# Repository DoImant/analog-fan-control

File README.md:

# Description:

This fan control circuit was realized with an LM317 voltage regulator. The circuit is suitable for fans that cannot be regulated via PWM (2 or 3-pin).
The maximum operating voltage is 12V. An NTC 10K 3950 (1%) with JST XH cable connector is used for temperature measurement.
The circuit board is equipped with a four-pin fan connector. If a fan with three pins is connected, the signal for the fan speed can be picked off at the free fourth pin (S. out) of the connector plug.

## Temperature setting:
Turn RV1 all the way to the right. Bring NTC to body temperature (hold with your fist), wait a little and then RV1
turn to the left until the fan starts to rotate. From the point three more half turns further.

Turn RV2 until the voltage at VAdjust is 4.7 to 4.8 volts.

With this setting method, the fan starts to run from around 36°C. As the temperature rises, the fan speed increases up to the maximum speed at around 70°C. If the temperature drops to approx. 26°C, the fan is switched off again.

## Pictures

First test setup on a breadboard

PCB (front)

PCB back

## circuit diagram
[circuit diagram](https://github.com/DoImant/Stuff/blob/main/Analog_fan_control/Luefter-Steuerung-Analog-V2.pdf)

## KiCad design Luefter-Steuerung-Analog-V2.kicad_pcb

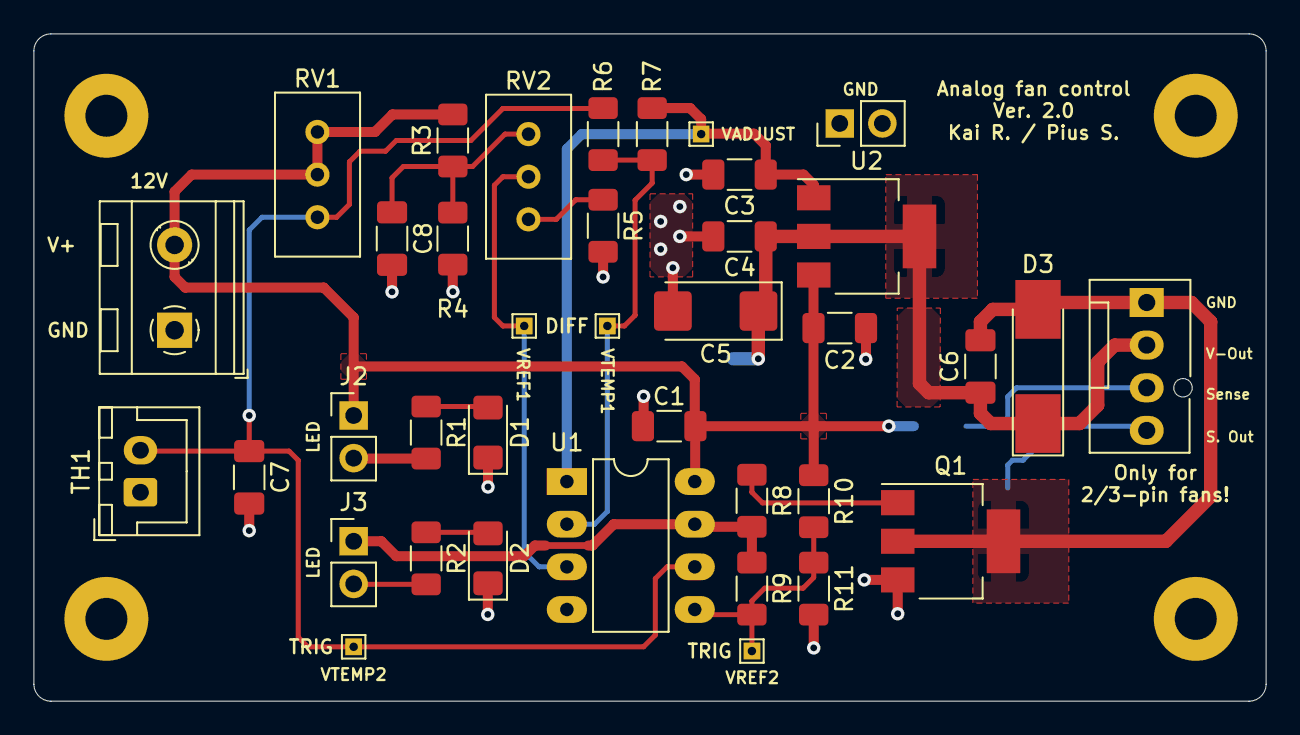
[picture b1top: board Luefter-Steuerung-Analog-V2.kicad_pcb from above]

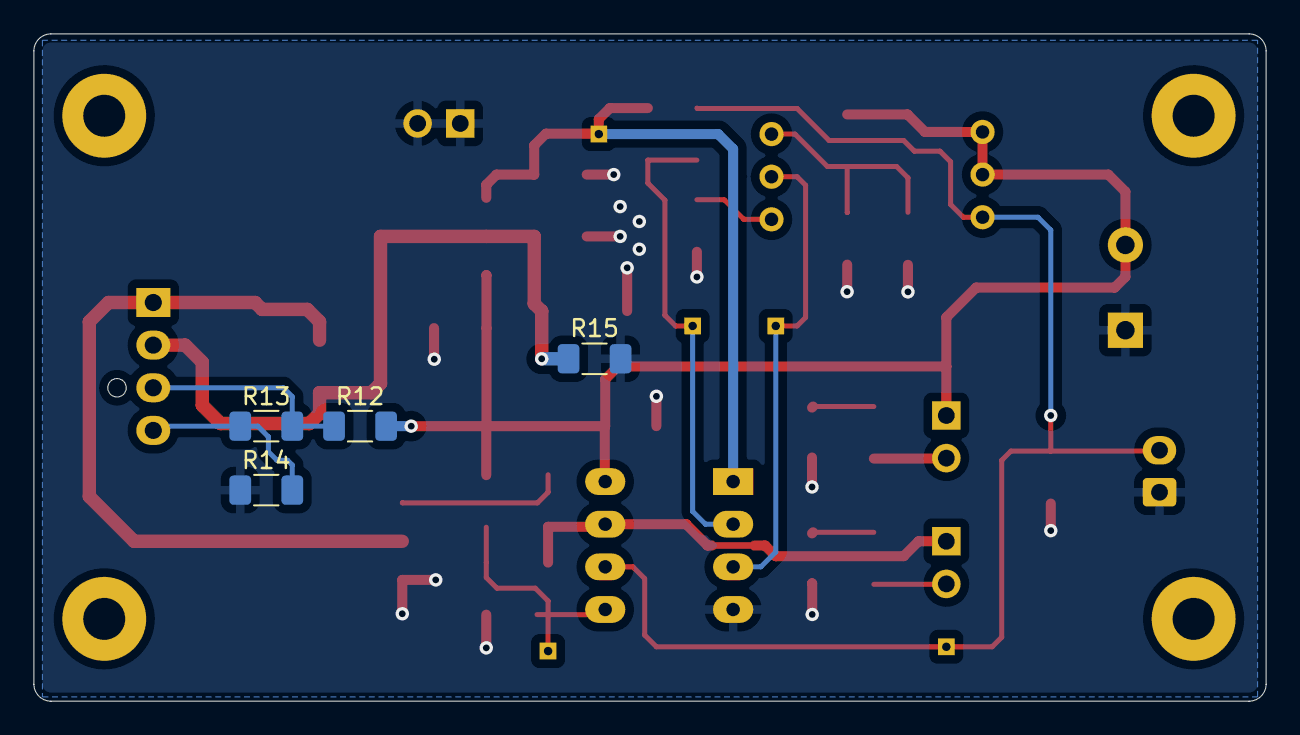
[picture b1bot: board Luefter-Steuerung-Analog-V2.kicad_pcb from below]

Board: 2 copper layers, 73.4 x 39.8 mm, 45 parts (4 on the bottom side), 19 nets.

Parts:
C1, C2, C4, C6: 100n; C_1206_3216Metric_Pad1.33x1.80mm_HandSolder
C3: 1u; C_1206_3216Metric_Pad1.33x1.80mm_HandSolder
C5: 10u; CP_EIA-6032-28_Kemet-C_Pad2.25x2.35mm_HandSolder
C7, C8: 10n; C_1206_3216Metric_Pad1.33x1.80mm_HandSolder
D1, D2: LED; LED_1206_3216Metric_Pad1.42x1.75mm_HandSolder
D3: 1N4001; D_MELF_Handsoldering
H1, H2, H3, H4: MountingHole; MountingHole_2.5mm_Pad
J1: Conn_01x02; TerminalBlock_RND_205-00232_1x02_P5.08mm_Horizontal
J2, J3: Conn_01x02; PinHeader_1x02_P2.54mm_Vertical
J4: Conn_01x04_Male; FanPinHeader_1x04_P2.54mm_Vertical
Q1: BCP56; SOT-223-3_TabPin2
R1, R2: 15k; R_1206_3216Metric_Pad1.30x1.75mm_HandSolder
R3, R10: 47k; R_1206_3216Metric_Pad1.30x1.75mm_HandSolder
R4, R15: 100k; R_1206_3216Metric_Pad1.30x1.75mm_HandSolder
R5: 82k; R_1206_3216Metric_Pad1.30x1.75mm_HandSolder
R6: 33k; R_1206_3216Metric_Pad1.30x1.75mm_HandSolder
R7: 68k; R_1206_3216Metric_Pad1.30x1.75mm_HandSolder
R8, R13, R14: 10k; R_1206_3216Metric_Pad1.30x1.75mm_HandSolder
R9: 270k; R_1206_3216Metric_Pad1.30x1.75mm_HandSolder
R11: 56k; R_1206_3216Metric_Pad1.30x1.75mm_HandSolder
R12: 4k7; R_1206_3216Metric_Pad1.30x1.75mm_HandSolder
RV1: 10k; Potentiometer_Bourns_3296W_Vertical
RV2: 20k; Potentiometer_Bourns_3296W_Vertical
TH1: 10k; JST_XH_B2B-XH-A_1x02_P2.50mm_Vertical
TP1, TP2, TP3, TP4, TP5: TestPoint; TestPoint_THTPad_1.0x1.0mm_Drill0.5mm
U1: LM358; DIP-8_W7.62mm_LongPads
U2: LM317_SOT-223; SOT-223-3_TabPin2

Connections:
+12V: C1.1, C2.1, J1.2, J2.1, R3.1, R10.1, R12.1, RV1.1, RV1.2, U1.8, U2.3
/SIG-Ref: C8.1, R3.2, R4.1, RV2.1
/SIG_Adjust: C3.1, R7.1, TP3.1, U1.1, U2.1
/SIG_REF(+): RV2.2, TP2.1, U1.3
/SIG_REF_TRIG: R9.2, R10.2, R11.1, TP4.1, U1.5
/SIG_TEMP(-): R6.2, R7.2, TP1.1, U1.2
/SIG_Temp: C7.1, R6.1, RV1.3, TH1.2, TP5.1, U1.6
/Sense: J4.3, R12.2, R13.1
/Sense_Out: J4.4, R13.2, R14.1
/TRIG_ON_OFF: J3.1, R8.2, R9.1, U1.7
/V-OUT: C4.1, C5.1, C6.1, D3.1, J4.2, R15.1, U2.2
GND: C1.2, C2.2, C3.2, C4.2, C5.2, C7.2, C8.2, D1.1, D2.1, J1.1, Q1.3, R4.2, R5.2, R11.2, R14.2, R15.2, TH1.1, U1.4
unnamed: C6.2, D3.2, J4.1, Q1.2
unnamed: D1.2, R1.1
unnamed: D2.2, R2.1
unnamed: J2.2, R1.2
unnamed: J3.2, R2.2
unnamed: Q1.1, R8.1
unnamed: R5.1, RV2.3

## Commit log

2022-06-20 README changed
